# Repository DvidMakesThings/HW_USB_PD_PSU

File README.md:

# USB-PD-PSU Project

## Contents
This folder contains all the documents related to the USB-PD-PSU project.

## Usage
To use the files in this project, navigate to the respective directories and follow the instructions provided in each document.

## License
This project is licensed under the GPL-3.0 License. See the [LICENSE](LICENSE) file for details.

## Contact
For questions or feedback:
- Email: [s.dvid@hotmail.com](mailto:s.dvid@hotmail.com)
- GitHub: [DvidMakesThings](https://github.com/DvidMakesThings)

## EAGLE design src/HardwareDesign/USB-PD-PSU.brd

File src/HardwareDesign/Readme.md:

# # USB-PD-PSU Project Hardware Design Files

## Contents
This folder contains the hardware design files for the USB-PD-PSU project. The main components include:
- Schematic diagrams
- PCB layouts
- Bill of Materials (BOM)
- Gerber files

## Usage
To use these hardware design files:
1. Open the schematic diagrams and PCB layouts using EAGLE software.
2. Review the Bill of Materials for required components.
3. Follow the design files to assemble and test the hardware.
4. Use the Gerber files for PCB manufacturing.

## License
This project is licensed under the GPL-3.0 License. See the [LICENSE](LICENSE) file for details.

## Contact
For questions or feedback:
- Email: [s.dvid@hotmail.com](mailto:s.dvid@hotmail.com)
- GitHub: [DvidMakesThings](https://github.com/DvidMakesThings)

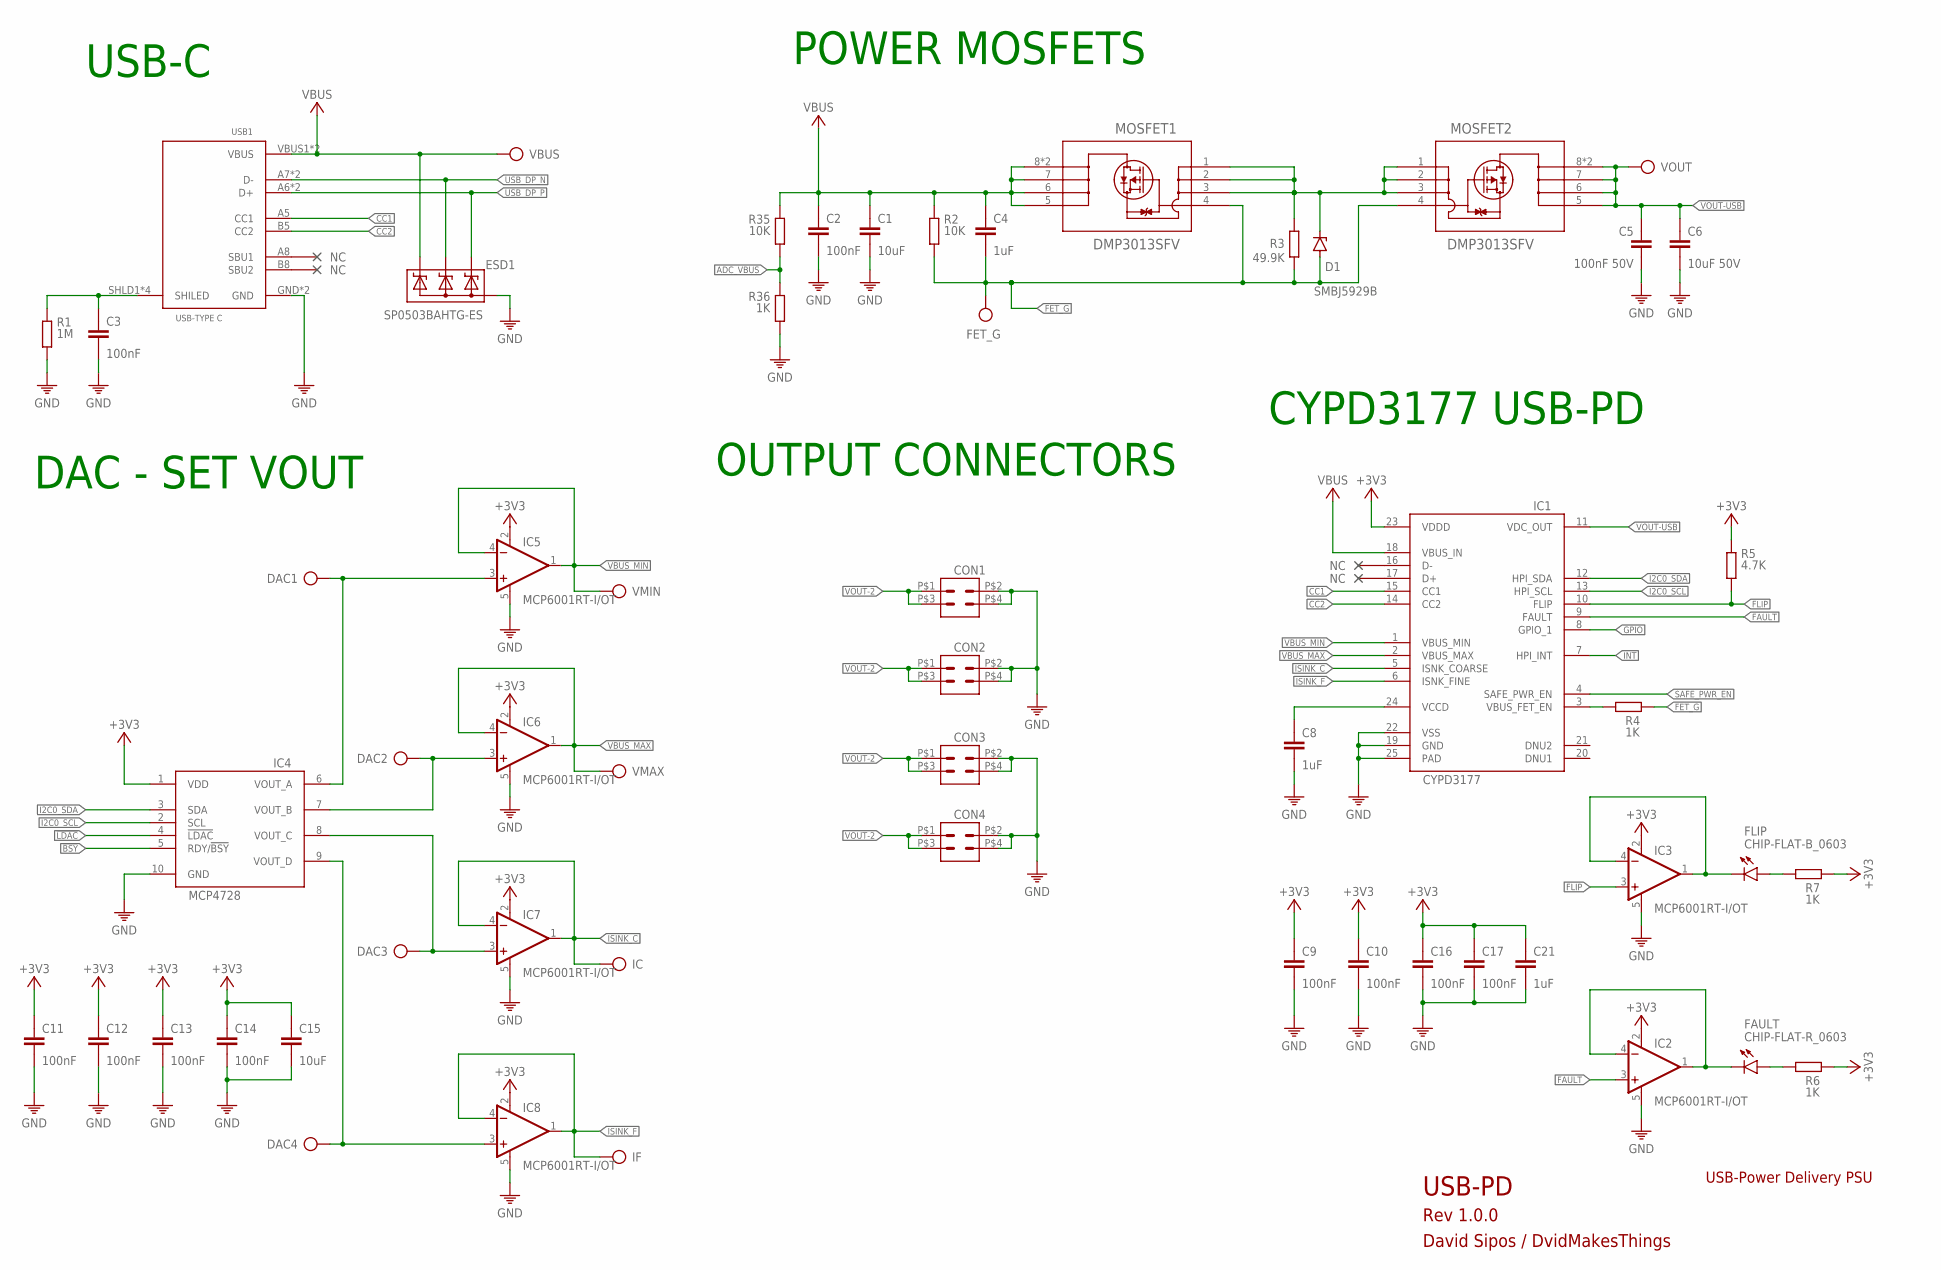
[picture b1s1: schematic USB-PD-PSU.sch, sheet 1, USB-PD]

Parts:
C1: 10uF; C0805
C2, C3: 100nF; C0603
C4: 1uF; C0603
C5: 100nF 50V; C0603
C6: 10uF 50V; C0603
C8, C21: 1uF; 0201
C9, C10, C11, C12, C13, C14, C16, C17: 100nF; 0201
C15: 10uF; 0201
CON1, CON2, CON3, CON4: CON-2X2SMD; 2X2_SMD
D1: SMBJ5929B; DIOM5226X290N
DAC1, DAC2, DAC3, DAC4: TP
ESD1: SP0503BAHTG-ES; SOT143
FAULT: CHIP-FLAT-R_0603; LEDC1608X55N_FLAT-R
FET_G: TP
FLIP: CHIP-FLAT-B_0603; LEDC1608X55N_FLAT-B
IC: TP
IC1: CYPD3177; QFN24
IC2, IC3, IC5, IC6, IC7, IC8: MCP6001RT-I/OT; SOT23-5
IC4: MCP4728; MSOP10
IF: TP
MOSFET1, MOSFET2: DMP3013SFV; POWERDI3333-8_UX_DIO-L
R1: 1M; 0402
R2, R35: 10K; 0402
R3: 49.9K; 0402
R4, R6, R7: 1K; R0201
R5: 4.7K; R0201
R36: 1K; 0402
USB1: USB_C-THT; USB-C
VBUS: TP
VMAX: TP
VMIN: TP
VOUT: TP

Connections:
!BSY: IC4.5 (RDY/!BSY); also elsewhere on the board
!LDAC: IC4.4 (!LDAC); also elsewhere on the board
+3V3: C9.1, C10.1, C11.1, C12.1, C13.1, C14.1, C15.1, C16.1, C17.1, C21.1, IC1.23 (VDDD), IC2.2 (V+), IC3.2 (V+), IC4.1 (VDD), IC5.2 (V+), IC6.2 (V+), IC7.2 (V+), IC8.2 (V+), R5.1, R6.1, R7.1; also elsewhere on the board
ADC_VBUS: R35.2, R36.1; also elsewhere on the board
CC1: IC1.15 (CC1), USB1.A5 (CC1)
CC2: IC1.14 (CC2), USB1.B5 (CC2)
FAULT: IC1.9 (FAULT), IC2.3 (+IN); also elsewhere on the board
FET_G: C4.2, D1.2 (A), FET_G.TP, MOSFET1.4 (G), MOSFET2.4 (G), R2.2, R3.2, R4.1
FLIP: IC1.10 (FLIP), IC3.3 (+IN), R5.2; also elsewhere on the board
GND: C1.2, C2.2, C3.2, C5.2, C6.2, C8.2, C9.2, C10.2, C11.2, C12.2, C13.2, C14.2, C15.2, C16.2, C17.2, C21.2, CON1.P$2 (2), CON1.P$4 (4), CON2.P$2 (2), CON2.P$4 (4), CON3.P$2 (2), CON3.P$4 (4), CON4.P$2 (2), CON4.P$4 (4), ESD1.1 (A), IC1.19 (GND), IC1.22 (VSS), IC1.25 (PAD), IC2.5 (V-), IC3.5 (V-), IC4.10 (GND), IC5.5 (V-), IC6.5 (V-), IC7.5 (V-), IC8.5 (V-), R1.2, R36.2, USB1.GND, USB1.GND2 (GND); also elsewhere on the board
GPIO: IC1.8 (GPIO_1)
I2C0_SCL: IC1.13 (HPI_SCL), IC4.2 (SCL); also elsewhere on the board
I2C0_SDA: IC1.12 (HPI_SDA), IC4.3 (SDA); also elsewhere on the board
INT: IC1.7 (HPI_INT); also elsewhere on the board
ISINK_C: IC.TP, IC1.5 (ISNK_COARSE), IC7.1 (OUT), IC7.4 (-IN)
ISINK_F: IC1.6 (ISNK_FINE), IC8.1 (OUT), IC8.4 (-IN), IF.TP
unnamed: C3.1, R1.1, USB1.SHLD1 (SHILED), USB1.SHLD2 (SHILED), USB1.SHLD3 (SHILED), USB1.SHLD4 (SHILED)
unnamed: FLIP.C, IC3.1 (OUT), IC3.4 (-IN)
unnamed: C8.1, IC1.24 (VCCD)
unnamed: IC1.3 (VBUS_FET_EN), R4.2
unnamed: D1.1 (C), MOSFET1.1 (S_2), MOSFET1.2 (S_3), MOSFET1.3 (S), MOSFET2.1 (S_2), MOSFET2.2 (S_3), MOSFET2.3 (S), R3.1
unnamed: FAULT.C, IC2.1 (OUT), IC2.4 (-IN)
unnamed: FLIP.A, R7.2
unnamed: FAULT.A, R6.2
unnamed: DAC1.TP, IC4.6 (VOUT_A), IC5.3 (+IN)
unnamed: DAC2.TP, IC4.7 (VOUT_B), IC6.3 (+IN)
unnamed: DAC3.TP, IC4.8 (VOUT_C), IC7.3 (+IN)
unnamed: DAC4.TP, IC4.9 (VOUT_D), IC8.3 (+IN)
SAFE_PWR_EN: IC1.4 (SAFE_PWR_EN)
USB_DP_N: ESD1.3 (C2), USB1.A7 (D-), USB1.B7 (D-); also elsewhere on the board
USB_DP_P: ESD1.2 (C1), USB1.A6 (D+), USB1.B6 (D+); also elsewhere on the board
VBUS: C1.1, C2.1, C4.1, ESD1.4 (C3), IC1.18 (VBUS_IN), MOSFET1.5 (D_2), MOSFET1.6 (D_3), MOSFET1.7 (D_4), MOSFET1.8 (D), MOSFET1.9 (D), R2.1, R35.1, USB1.VBUS1 (VBUS), USB1.VBUS2 (VBUS), VBUS.TP; also elsewhere on the board
VBUS_MAX: IC1.2 (VBUS_MAX), IC6.1 (OUT), IC6.4 (-IN), VMAX.TP
VBUS_MIN: IC1.1 (VBUS_MIN), IC5.1 (OUT), IC5.4 (-IN), VMIN.TP
VOUT-2: CON1.P$1 (1), CON1.P$3 (3), CON2.P$1 (1), CON2.P$3 (3), CON3.P$1 (1), CON3.P$3 (3), CON4.P$1 (1), CON4.P$3 (3); also elsewhere on the board
VOUT-USB: C5.1, C6.1, IC1.11 (VDC_OUT), MOSFET2.5 (D_2), MOSFET2.6 (D_3), MOSFET2.7 (D_4), MOSFET2.8 (D), MOSFET2.9 (D), VOUT.TP; also elsewhere on the board

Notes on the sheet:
CYPD3177 USB-PD
USB-C
POWER MOSFETS
DAC - SET VOUT
USB-PD
Rev 1.0.0
David Sipos / DvidMakesThings
USB-Power Delivery PSU
OUTPUT CONNECTORS

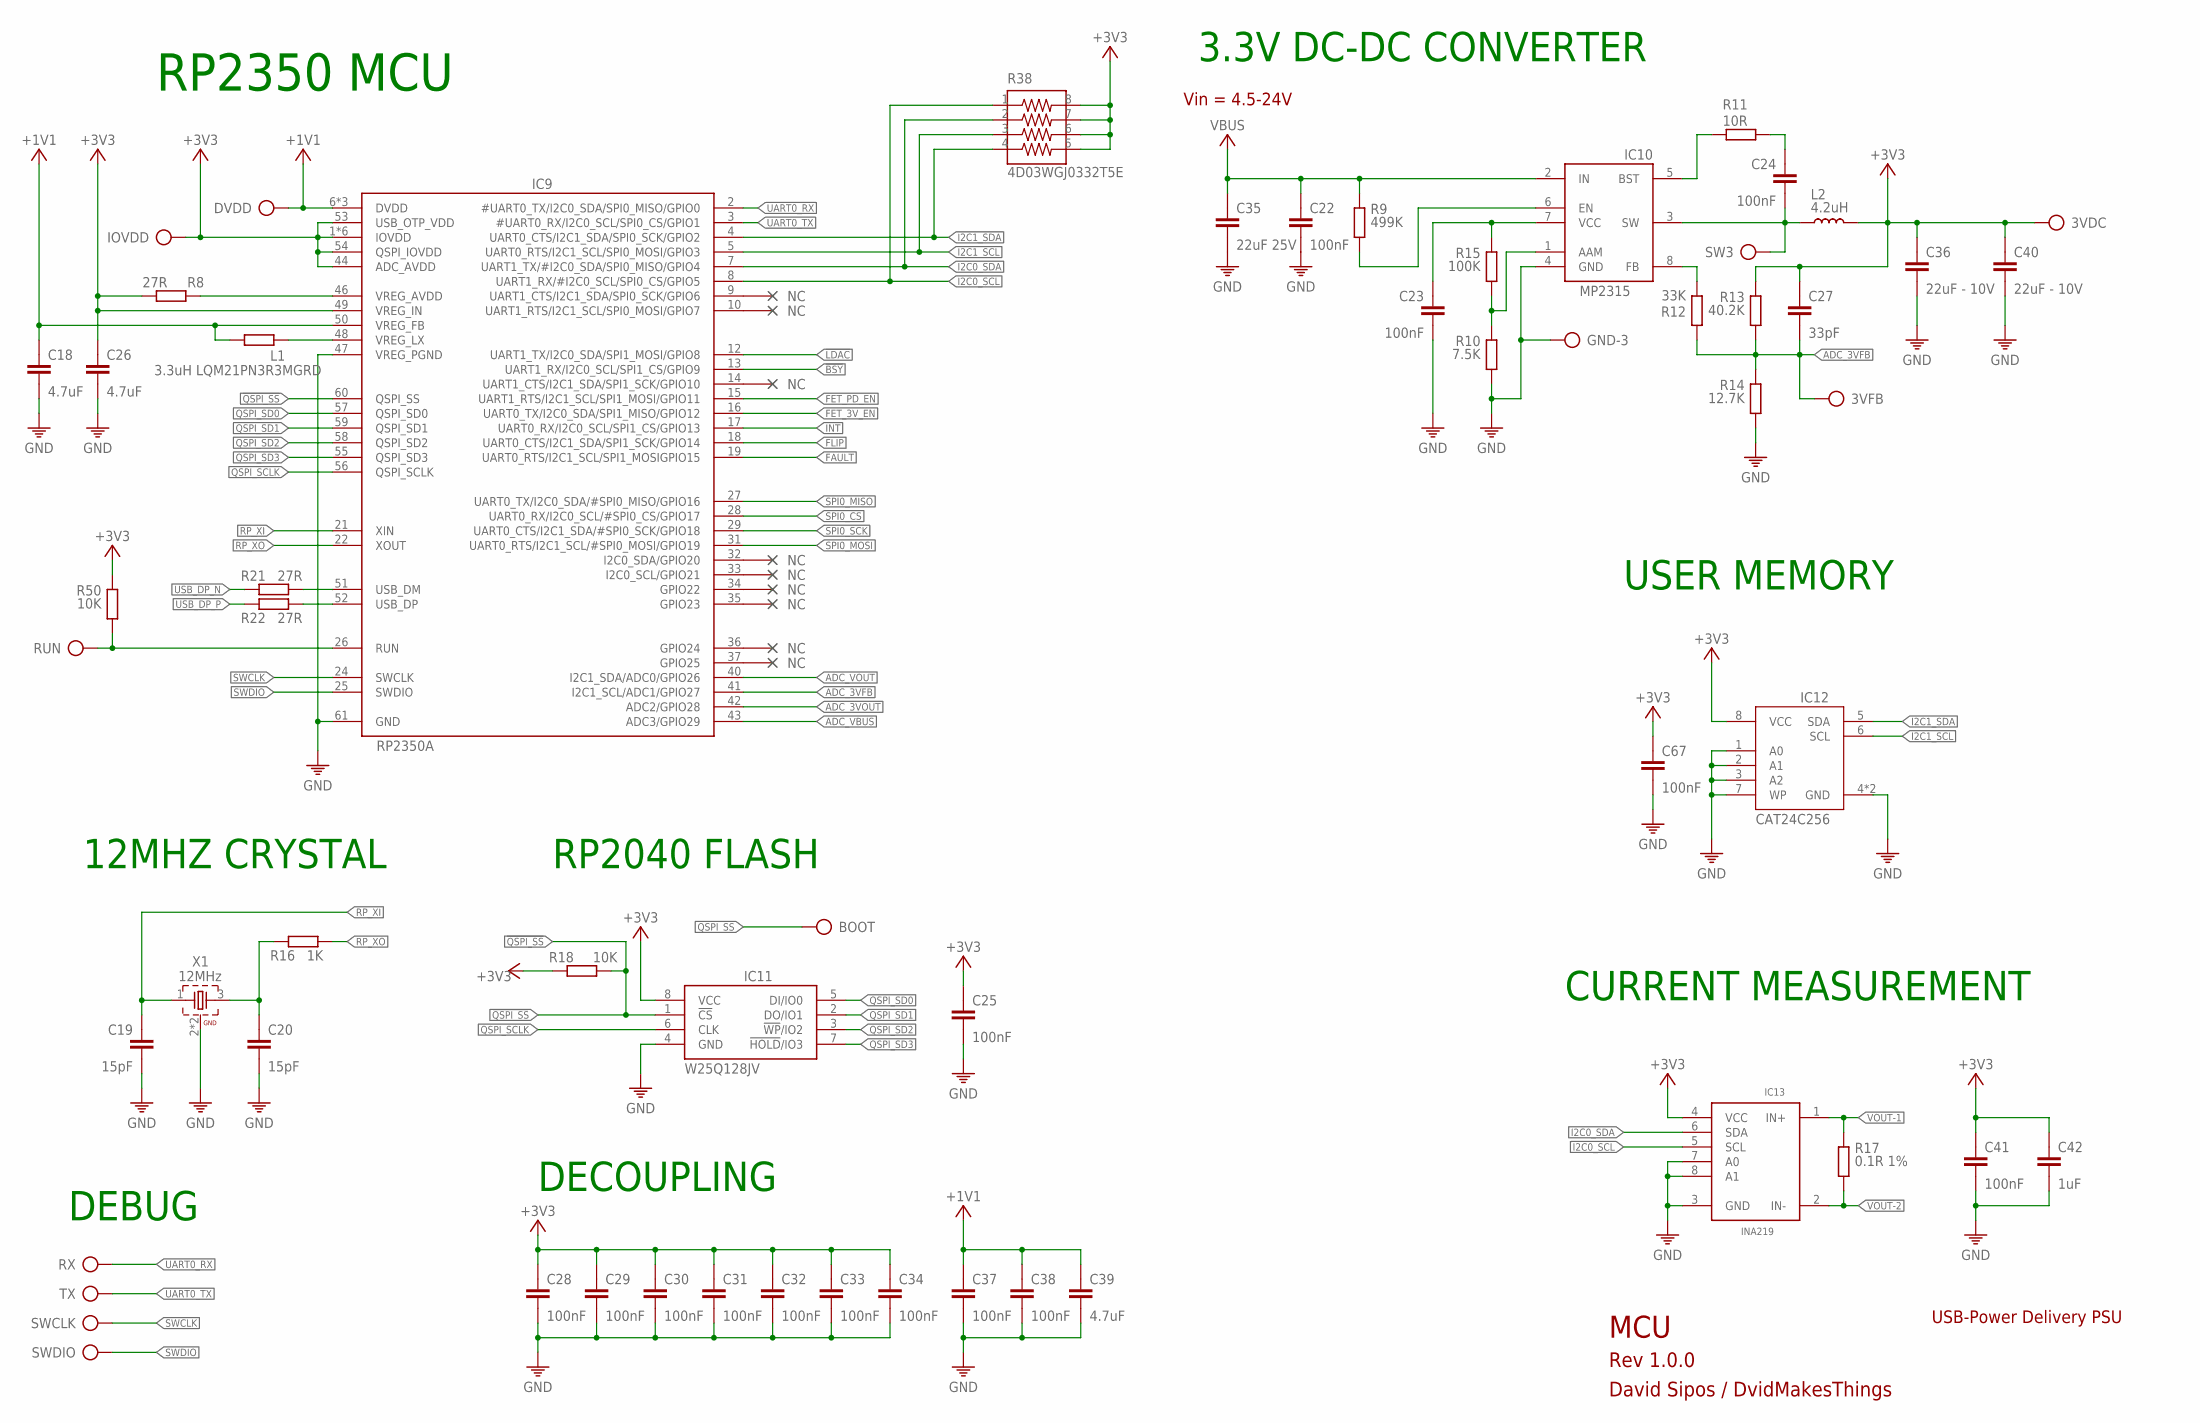
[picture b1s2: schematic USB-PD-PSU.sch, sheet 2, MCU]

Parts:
3VDC, 3VFB: TP
BOOT: TP
C18, C26, C39: 4.7uF; 0201
C19, C20: 15pF; C0402
C22, C23, C24: 100nF; 0402
C25: 100nF; C0402
C27: 33pF; 0402
C28, C29, C30, C31, C32, C33, C34, C37, C38, C41, C67: 100nF; 0201
C35: 22uF 25V; C1206
C36, C40: 22uF - 10V; C1206
C42: 1uF; 0201
DVDD: TP
GND-3: TP
IC9: RP2350AA; QFN40P700X700X85-61T340N
IC10: MP2315S; SOT65P280X110-8N
IC11: W25Q128JVPIQ; SON127P600X500X75-8N
IC12: CAT24C512HU5IGT3; SON50P300X200X50-9T130X140N
IC13: INA219BIDCNT; SOT23-8
IOVDD: TP
L1: 3.3uH LQM21PN3R3MGRD; 0805
L2: 4.2uH; SRR5228A
R8, R21, R22: 27R; R0201
R9: 499K; 0402
R10: 7.5K; 0402
R11: 10R; 0402
R12: 33K; 0402
R13: 40.2K; 0402
R14: 12.7K; 0402
R15: 100K; 0402
R16: 1K; R0201
R17: 0.1R 1%; 2512
R18, R50: 10K; 0402
R38: 4D03WGJ0332T5E; 742C083103JP
RUN: TP
RX: TP
SW3: TP
SWCLK: TP
SWDIO: TP
TX: TP
X1: 12MHz; WE-XTAL_CFPX-180

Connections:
!BSY: IC9.13 (UART1_RX/I2C0_SCL/SPI1_CS/GPIO9); also elsewhere on the board
!LDAC: IC9.12 (UART1_TX/I2C0_SDA/SPI1_MOSI/GPIO8); also elsewhere on the board
!QSPI_SS: BOOT.TP, IC9.60 (QSPI_SS), IC11.1 (!CS), R18.1
+1V1: C18.1, C37.1, C38.1, C39.1, DVDD.TP, IC9.6 (DVDD), IC9.23 (DVDD), IC9.39 (DVDD), IC9.50 (VREG_FB), L1.2
+3V3: 3VDC.TP, C25.1, C26.1, C27.1, C28.1, C29.1, C30.1, C31.1, C32.1, C33.1, C34.1, C36.1, C40.1, C41.1, C42.1, C67.1, IC9.1 (IOVDD), IC9.11 (IOVDD), IC9.20 (IOVDD), IC9.30 (IOVDD), IC9.38 (IOVDD), IC9.44 (ADC_AVDD), IC9.45 (IOVDD), IC9.49 (VREG_IN), IC9.53 (USB_OTP_VDD), IC9.54 (QSPI_IOVDD), IC11.8 (VCC), IC12.8 (VCC), IC13.4 (VCC), IOVDD.TP, L2.2, R8.2, R13.1, R18.2, R38.5, R38.6, R38.7, R38.8, R50.1; also elsewhere on the board
ADC_3VFB: 3VFB.TP, C27.2, IC9.41 (I2C1_SCL/ADC1/GPIO27), R12.2, R13.2, R14.1
ADC_3VOUT: IC9.42 (ADC2/GPIO28); also elsewhere on the board
ADC_VBUS: IC9.43 (ADC3/GPIO29); also elsewhere on the board
ADC_VOUT: IC9.40 (I2C1_SDA/ADC0/GPIO26); also elsewhere on the board
FAULT: IC9.19 (UART0_RTS/I2C1_SCL/SPI1_MOSIGPIO15); also elsewhere on the board
FET_3V_EN: IC9.16 (UART0_TX/I2C0_SDA/SPI1_MISO/GPIO12); also elsewhere on the board
FET_PD_EN: IC9.15 (UART1_RTS/I2C1_SCL/SPI1_MOSI/GPIO11); also elsewhere on the board
FLIP: IC9.18 (UART0_CTS/I2C1_SDA/SPI1_SCK/GPIO14); also elsewhere on the board
GND: C18.2, C19.2, C20.2, C22.2, C23.2, C25.2, C26.2, C28.2, C29.2, C30.2, C31.2, C32.2, C33.2, C34.2, C35.2, C36.2, C37.2, C38.2, C39.2, C40.2, C41.2, C42.2, C67.2, GND-3.TP, IC9.47 (VREG_PGND), IC9.61 (GND), IC10.4 (GND), IC11.4 (GND), IC12.1 (A0), IC12.2 (A1), IC12.3 (A2), IC12.4 (GND), IC12.7 (WP), IC12.9 (GND), IC13.3 (GND), IC13.7 (A0), IC13.8 (A1), R10.2, R14.2, X1.2 (GND), X1.4 (GND); also elsewhere on the board
I2C0_SCL: IC9.8 (UART1_RX/#I2C0_SCL/SPI0_CS/GPIO5), IC13.5 (SCL), R38.1; also elsewhere on the board
I2C0_SDA: IC9.7 (UART1_TX/#I2C0_SDA/SPI0_MISO/GPIO4), IC13.6 (SDA), R38.2; also elsewhere on the board
I2C1_SCL: IC9.5 (UART0_RTS/I2C1_SCL/SPI0_MOSI/GPIO3), IC12.6 (SCL), R38.3; also elsewhere on the board
I2C1_SDA: IC9.4 (UART0_CTS/I2C1_SDA/SPI0_SCK/GPIO2), IC12.5 (SDA), R38.4; also elsewhere on the board
INT: IC9.17 (UART0_RX/I2C0_SCL/SPI1_CS/GPIO13); also elsewhere on the board
MCU_DP_N: IC9.51 (USB_DM), R21.2
MCU_DP_P: IC9.52 (USB_DP), R22.2
unnamed: C20.1, R16.1, X1.3 (2)
unnamed: IC9.46 (VREG_AVDD), R8.1
unnamed: IC9.48 (VREG_LX), L1.1
unnamed: IC9.26 (RUN), R50.2, RUN.TP
unnamed: IC10.5 (BST), R11.2
unnamed: IC10.8 (FB), R12.1
unnamed: C24.1, R11.1
unnamed: IC10.6 (EN), R9.2
unnamed: C23.1, IC10.7 (VCC), R15.1
unnamed: IC10.1 (AAM), R10.1, R15.2
QSPI_SCLK: IC9.56 (QSPI_SCLK), IC11.6 (CLK)
QSPI_SD0: IC9.57 (QSPI_SD0), IC11.5 (DI/IO0)
QSPI_SD1: IC9.59 (QSPI_SD1), IC11.2 (DO/IO1)
QSPI_SD2: IC9.58 (QSPI_SD2), IC11.3 (!WP!/IO2)
QSPI_SD3: IC9.55 (QSPI_SD3), IC11.7 (!HOLD!/IO3)
RP_XI: C19.1, IC9.21 (XIN), X1.1
RP_XO: IC9.22 (XOUT), R16.2
SPI0_CS: IC9.28 (UART0_RX/I2C0_SCL/#SPI0_CS/GPIO17)
SPI0_MISO: IC9.27 (UART0_TX/I2C0_SDA/#SPI0_MISO/GPIO16)
SPI0_MOSI: IC9.31 (UART0_RTS/I2C1_SCL/#SPI0_MOSI/GPIO19)
SPI0_SCK: IC9.29 (UART0_CTS/I2C1_SDA/#SPI0_SCK/GPIO18)
SW3: C24.2, IC10.3 (SW), L2.1, SW3.TP
SWCLK: IC9.24 (SWCLK), SWCLK.TP
SWDIO: IC9.25 (SWDIO), SWDIO.TP
UART0_RX: IC9.2 (#UART0_TX/I2C0_SDA/SPI0_MISO/GPIO0), RX.TP
UART0_TX: IC9.3 (#UART0_RX/I2C0_SCL/SPI0_CS/GPIO1), TX.TP
USB_DP_N: R21.1; also elsewhere on the board
USB_DP_P: R22.1; also elsewhere on the board
VBUS: C22.1, C35.1, IC10.2 (IN), R9.1; also elsewhere on the board
VOUT-1: IC13.1 (IN+), R17.1; also elsewhere on the board
VOUT-2: IC13.2 (IN-), R17.2; also elsewhere on the board

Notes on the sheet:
DECOUPLING
12MHZ CRYSTAL
RP2350 MCU
RP2040 FLASH
USER MEMORY
DEBUG
MCU
Rev 1.0.0
David Sipos / DvidMakesThings
USB-Power Delivery PSU
3.3V DC-DC CONVERTER
Vin = 4.5-24V
CURRENT MEASUREMENT

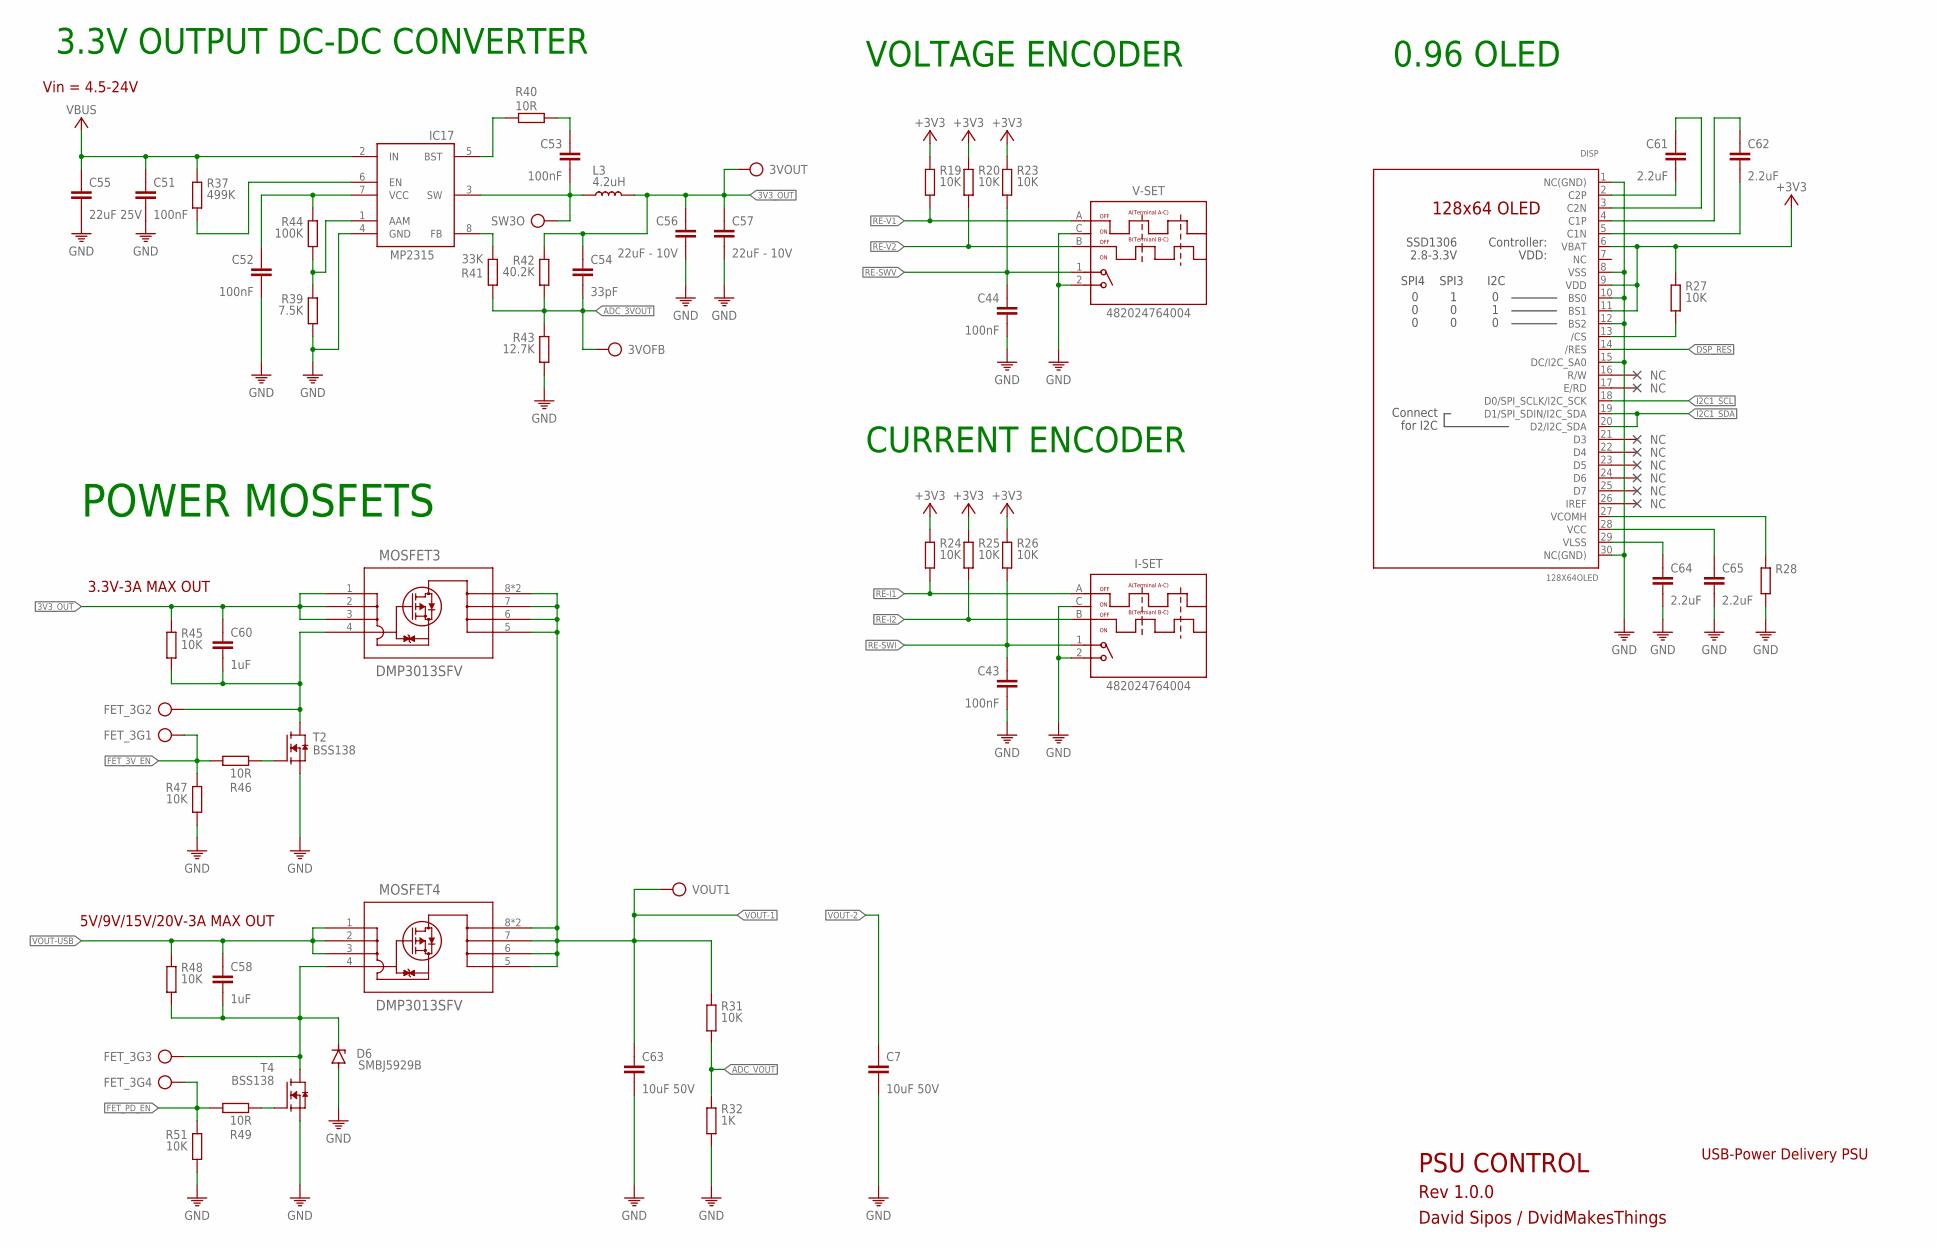
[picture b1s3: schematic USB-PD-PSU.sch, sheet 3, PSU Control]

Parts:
3VOFB, 3VOUT: TP
C7: 10uF 50V; C0805
C43, C44: 100nF; 0201
C51, C52, C53: 100nF; 0402
C54: 33pF; 0402
C55: 22uF 25V; C1206
C56, C57: 22uF - 10V; C1206
C58, C60: 1uF; C0603
C61, C62, C64, C65: 2.2uF; 0201
C63: 10uF 50V; C0603
D6: SMBJ5929B; DIOM5226X290N
DISP: 128X64OLED; UG2864
FET_3G1, FET_3G2, FET_3G3, FET_3G4: TP
I-SET: 482024764004; WS-ENTV_482024764004
IC17: MP2315S; SOT65P280X110-8N
L3: 4.2uH; SRR5228A
MOSFET3, MOSFET4: DMP3013SFV; POWERDI3333-8_UX_DIO-L
R19, R20, R23, R24, R25, R26, R27: 10K; R0201
R28: R0201
R31, R45, R47, R48, R51: 10K; 0402
R32: 1K; 0402
R37: 499K; 0402
R39: 7.5K; 0402
R40, R46, R49: 10R; 0402
R41: 33K; 0402
R42: 40.2K; 0402
R43: 12.7K; 0402
R44: 100K; 0402
SW3O: TP
T2, T4: BSS138; SOT23
V-SET: 482024764004; WS-ENTV_482024764004
VOUT1: TP

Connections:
3V3_OUT: 3VOUT.TP, C54.1, C56.1, C57.1, C60.1, L3.2, MOSFET3.1 (S_2), MOSFET3.2 (S_3), MOSFET3.3 (S), R42.1, R45.1
+3V3: DISP.6 (VBAT), DISP.9 (VDD), DISP.11 (BS1), R19.1, R20.1, R23.1, R24.1, R25.1, R26.1, R27.1; also elsewhere on the board
ADC_3VOUT: 3VOFB.TP, C54.2, R41.2, R42.2, R43.1; also elsewhere on the board
ADC_VOUT: R31.2, R32.1; also elsewhere on the board
DSP_RES: DISP.14 (/RES)
FET_3V_EN: FET_3G1.TP, R46.1, R47.1; also elsewhere on the board
FET_G1: C60.2, FET_3G2.TP, MOSFET3.4 (G), R45.2, T2.3 (D)
FET_G2: C58.2, D6.1 (C), FET_3G3.TP, MOSFET4.4 (G), R48.2, T4.3 (D)
FET_PD_EN: FET_3G4.TP, R49.1, R51.1; also elsewhere on the board
GND: C7.2, C43.2, C44.2, C51.2, C52.2, C55.2, C56.2, C57.2, C63.2, C64.2, C65.2, D6.2 (A), DISP.1 (NC(GND)), DISP.8 (VSS), DISP.10 (BS0), DISP.12 (BS2), DISP.15 (DC/I2C_SA0), DISP.30 (NC(GND)), I-SET.2, I-SET.C (COM), IC17.4 (GND), R28.2, R32.2, R39.2, R43.2, R47.2, R51.2, T2.2 (S), T4.2 (S), V-SET.2, V-SET.C (COM); also elsewhere on the board
I2C1_SCL: DISP.18 (D0/SPI_SCLK/I2C_SCK); also elsewhere on the board
I2C1_SDA: DISP.19 (D1/SPI_SDIN/I2C_SDA), DISP.20 (D2/I2C_SDA); also elsewhere on the board
unnamed: C61.2, DISP.2 (C2P)
unnamed: C61.1, DISP.3 (C2N)
unnamed: C62.1, DISP.4 (C1P)
unnamed: C62.2, DISP.5 (C1N)
unnamed: DISP.13 (/CS), R27.2
unnamed: IC17.5 (BST), R40.2
unnamed: IC17.8 (FB), R41.1
unnamed: C53.1, R40.1
unnamed: IC17.6 (EN), R37.2
unnamed: C52.1, IC17.7 (VCC), R44.1
unnamed: IC17.1 (AAM), R39.1, R44.2
unnamed: R46.2, T2.1 (G)
unnamed: DISP.27 (VCOMH), R28.1
unnamed: C65.1, DISP.28 (VCC)
unnamed: R49.2, T4.1 (G)
unnamed: C64.1, DISP.29 (VLSS)
RE-I1: I-SET.A, R24.2
RE-I2: I-SET.B, R25.2
RE-SWI: C43.1, I-SET.1, R26.2
RE-SWV: C44.1, R23.2, V-SET.1
RE-V1: R19.2, V-SET.A
RE-V2: R20.2, V-SET.B
SW1: C53.2, IC17.3 (SW), L3.1, SW3O.TP
VBUS: C51.1, C55.1, IC17.2 (IN), R37.1; also elsewhere on the board
VOUT-1: C63.1, MOSFET3.5 (D_2), MOSFET3.6 (D_3), MOSFET3.7 (D_4), MOSFET3.8 (D), MOSFET3.9 (D), MOSFET4.5 (D_2), MOSFET4.6 (D_3), MOSFET4.7 (D_4), MOSFET4.8 (D), MOSFET4.9 (D), R31.1, VOUT1.TP; also elsewhere on the board
VOUT-2: C7.1; also elsewhere on the board
VOUT-USB: C58.1, MOSFET4.1 (S_2), MOSFET4.2 (S_3), MOSFET4.3 (S), R48.1; also elsewhere on the board

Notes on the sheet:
VOLTAGE ENCODER
CURRENT ENCODER
3.3V OUTPUT DC-DC CONVERTER
Vin = 4.5-24V
POWER MOSFETS
3.3V-3A MAX OUT
5V/9V/15V/20V-3A MAX OUT
0.96 OLED
PSU CONTROL
Rev 1.0.0
David Sipos / DvidMakesThings
USB-Power Delivery PSU

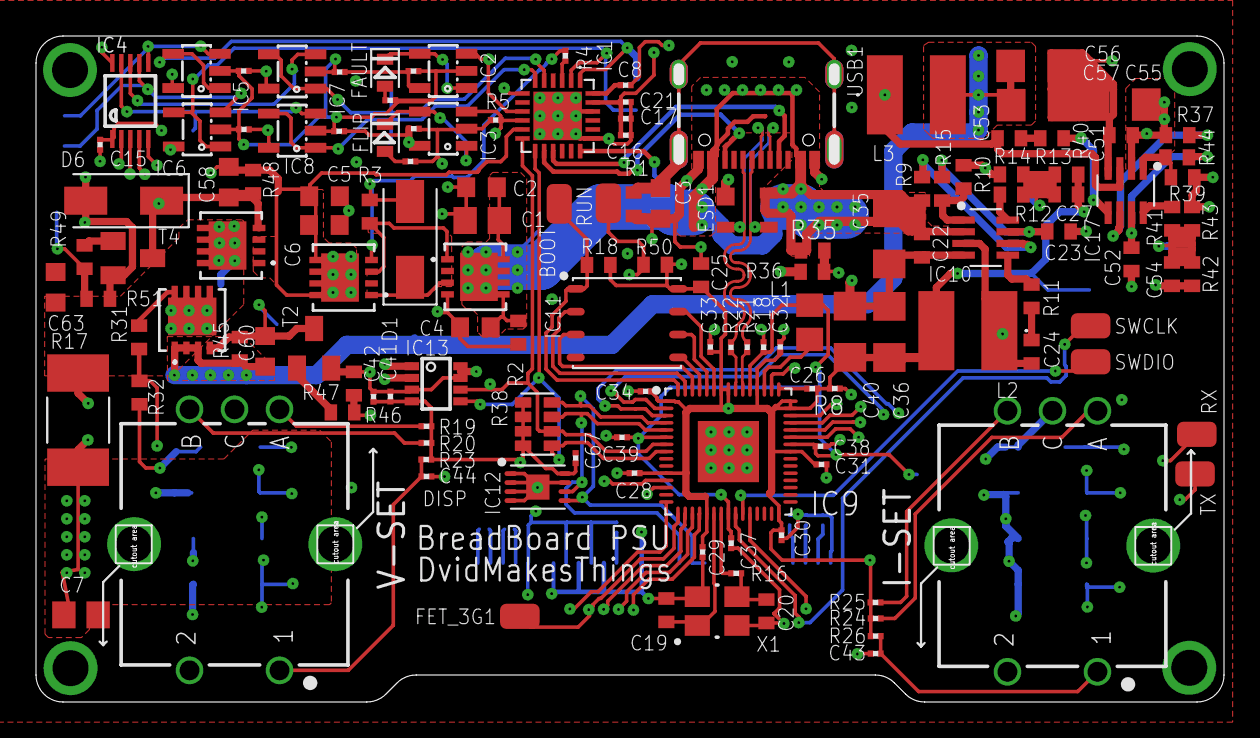
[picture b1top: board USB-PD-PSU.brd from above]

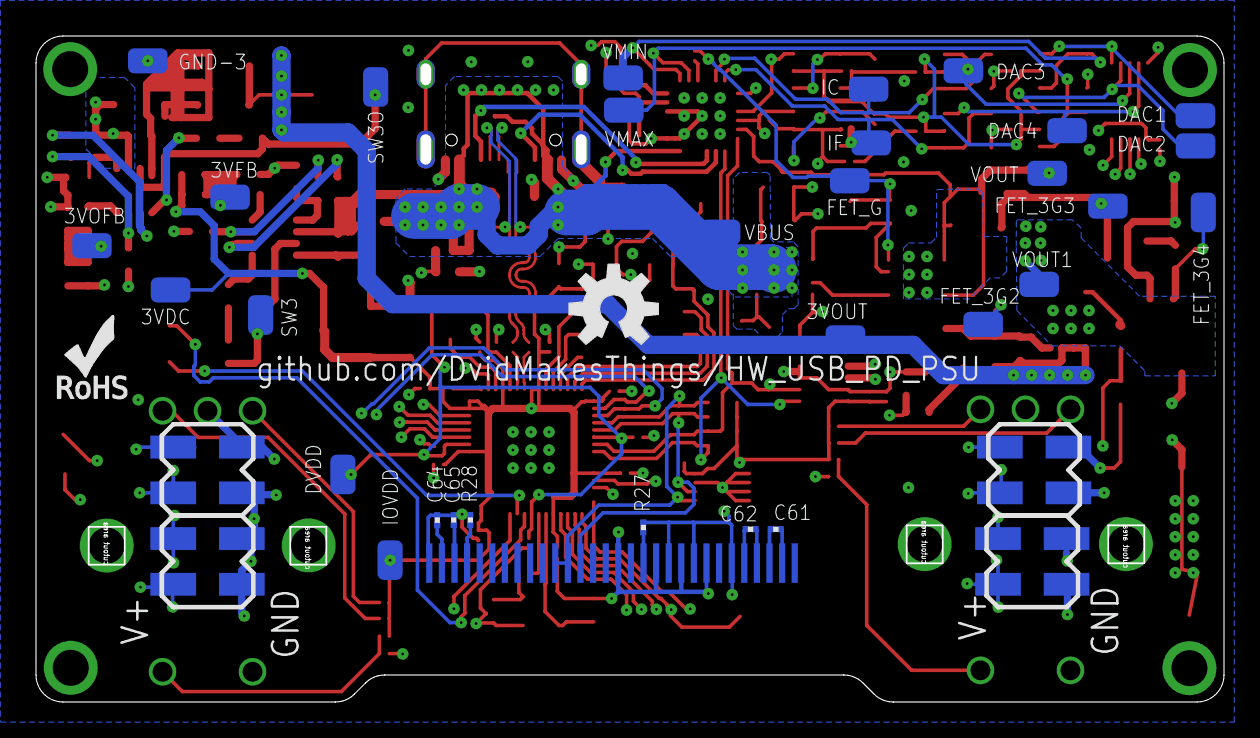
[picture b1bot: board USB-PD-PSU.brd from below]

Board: 4 copper layers, 65.4 x 36.4 mm, 176 parts (36 on the bottom side), 94 nets.

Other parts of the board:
U$1: ROHS_LOGO_0.18_IN
U$2: OSHW-LOGO-M

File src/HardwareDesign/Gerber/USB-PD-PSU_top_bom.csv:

Comment,Designator,Footprint,LCSC Part #
,IC9,QFN40P700X700X85-61T340N,
,USB1,USB-C,
0.1R 1%,R17,2512,
1K,R4 R6 R7 R16,R0201,
1K,R32 R36,0402,
1M,R1,0402,
1uF,C4,C0603,
1uF,C8 C21 C42,0201,
1uF,C58 C60,C0603,
3.3uH LQM21PN3R3MGRD,L1,0805,
4.2uH,L2 L3,SRR5228A,
4.7K,R5,R0201,
4.7uF,C18 C26 C39,0201,
4D03WGJ0332T5E,R38,742C083103JP,
7.5K,R10 R39,0402,
10K,R2 R18,0402,
10K,R19 R20 R23 R24 R25 R26,R0201,
10K,R31 R35 R45 R47 R48 R50 R51,0402,
10R,R11 R40 R46 R49,0402,
10uF,C1,C0805,
10uF,C15,0201,
10uF 50V,C6,C0603,
10uF 50V,C7,C0805,
10uF 50V,C63,C0603,
12.7K,R14 R43,0402,
12MHz,X1,WE-XTAL_CFPX-180,
15pF,C19 C20,C0402,
22uF - 10V,C36 C40 C56 C57,C1206,
22uF 25V,C35 C55,C1206,
27R,R8 R21 R22,R0201,
33K,R12 R41,0402,
33pF,C27 C54,0402,
40.2K,R13 R42,0402,
49.9K,R3,0402,
100K,R15 R44,0402,
100nF,C2 C3,C0603,
100nF,C9 C10 C11 C12 C13 C14 C16 C17,0201,
100nF,C22 C23 C24,0402,
100nF,C25,C0402,
100nF,C28 C29 C30 C31 C32 C33 C34 C37 C38 C41 C43 C44,0201,
100nF,C51 C52 C53,0402,
100nF,C67,0201,
100nF 50V,C5,C0603,
499K,R9 R37,0402,
BSS138,T2 T4,SOT23,
CAT24C512HU5IGT3,IC12,SON50P300X200X50-9T130X140N,
CHIP-FLAT-B_0603,FLIP,LEDC1608X55N_FLAT-B,
CHIP-FLAT-R_0603,FAULT,LEDC1608X55N_FLAT-R,
CYPD3177,IC1,QFN24,
DMP3013SFV,MOSFET1 MOSFET2 MOSFET3 MOSFET4,POWERDI3333-8_UX_DIO-L,
INA219BIDCNT,IC13,SOT23-8,
MCP4728,IC4,MSOP10,
MCP6001RT-I/OT,IC2 IC3 IC5 IC6 IC7 IC8,SOT23-5,
MP2315S ,IC10 IC17,SOT65P280X110-8N,
SMBJ5929B,D1 D6,DIOM5226X290N,
SP0503BAHTG-ES,ESD1,SOT143,
TP,BOOT FET_3G1 RUN RX SWCLK SWDIO TX,TP,
W25Q128JVPIQ,IC11,SON127P600X500X75-8N,

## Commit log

2025-03-13 Add initial project structure and documentation for USB-PD-PSU
2025-03-13 finished sch. Review needed
2025-03-14 PCB design ready

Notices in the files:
parts and their libraries:
Wurth_Switch_WS-ENTV: Copyright: Würth Elektronik
SparkFun-Aesthetics: Licensing: Creative Commons ShareAlike 4.0 International - https://creativecommons.org/licenses/by-sa/4.0
COPYRIGHT: Copyright (C) 2025 Ultra Librarian. All rights reserved.
